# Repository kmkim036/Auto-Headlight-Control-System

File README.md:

# Program Language  
C    
# When  
Senior, 2nd semester in Automobile Electric System Design Class  
# Description  
## Automatic Headlight Control System
Measure data with Light sensor and Acceleration sensor  

Control LED and Servo Motor  

Use CAN communication to command

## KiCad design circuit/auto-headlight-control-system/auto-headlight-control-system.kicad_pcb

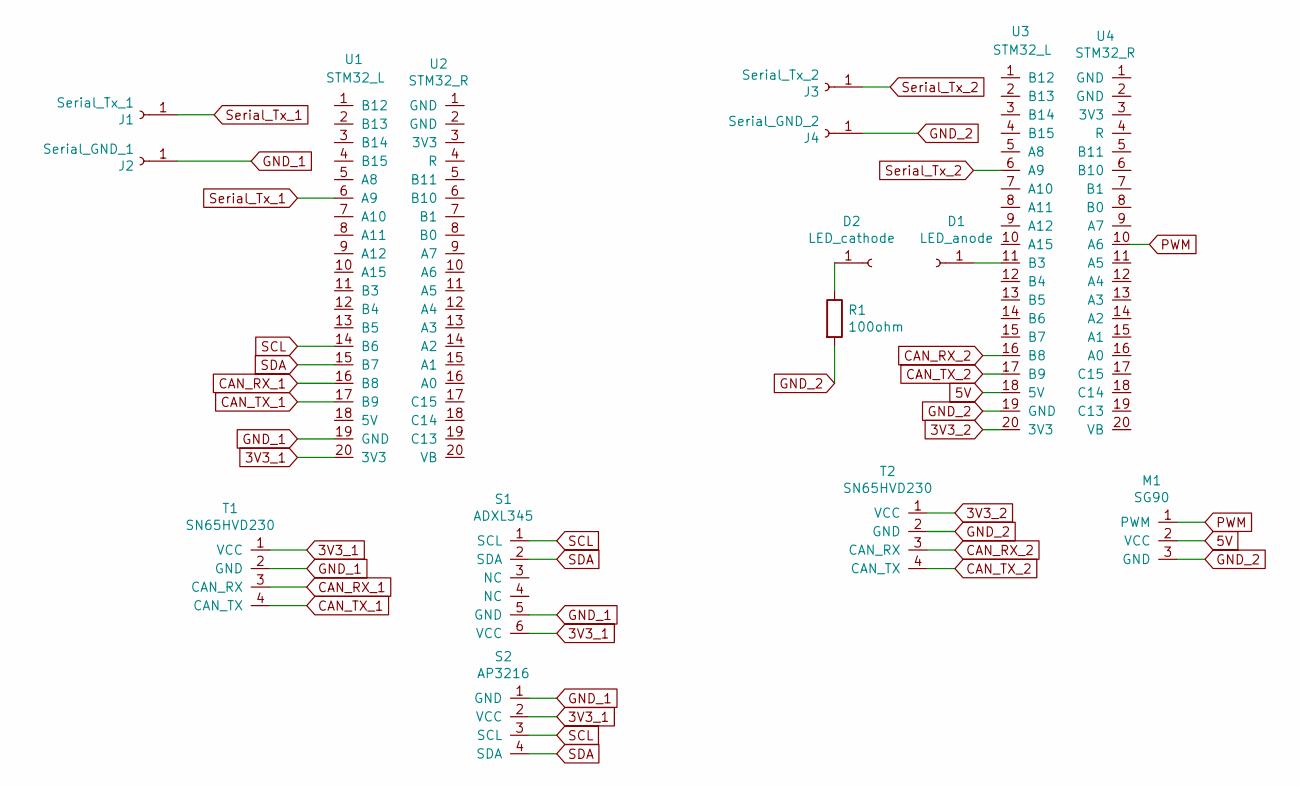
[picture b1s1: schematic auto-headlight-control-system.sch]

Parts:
D1: LED_anode; PinHeader_1x01_P2.54mm_Vertical
D2: LED_cathode; PinHeader_1x01_P2.54mm_Vertical
J1: Serial_Tx_1; PinSocket_1x01_P2.54mm_Vertical
J2: Serial_GND_1; PinSocket_1x01_P2.54mm_Vertical
J3: Serial_Tx_2; PinSocket_1x01_P2.54mm_Vertical
J4: Serial_GND_2; PinSocket_1x01_P2.54mm_Vertical
M1: SG90; PinHeader_1x03_P2.54mm_Vertical
R1: 100ohm; R_Axial_DIN0207_L6.3mm_D2.5mm_P2.54mm_Vertical
S1: ADXL345; PinHeader_1x06_P2.54mm_Vertical
S2: AP3216; PinHeader_1x04_P2.54mm_Vertical
T1, T2: SN65HVD230; PinHeader_1x04_P2.54mm_Vertical
U1, U3: STM32_L; PinHeader_1x20_P2.54mm_Vertical
U2, U4: STM32_R; PinHeader_1x20_P2.54mm_Vertical

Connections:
3V3_1: S1.6 (VCC), S2.2 (VCC), T1.1 (VCC), U1.20 (3V3)
3V3_2: T2.1 (VCC), U3.20 (3V3)
5V: M1.2 (VCC), U3.18 (5V)
CAN_RX_1: T1.3 (CAN_RX), U1.16 (B8)
CAN_RX_2: T2.3 (CAN_RX), U3.16 (B8)
CAN_TX_1: T1.4 (CAN_TX), U1.17 (B9)
CAN_TX_2: T2.4 (CAN_TX), U3.17 (B9)
GND_1: J2.1, S1.5 (GND), S2.1 (GND), T1.2 (GND), U1.19 (GND)
GND_2: J4.1, M1.3 (GND), R1.2, T2.2 (GND), U3.19 (GND)
unnamed: D1.1, U3.11 (B3)
unnamed: D2.1, R1.1
PWM: M1.1 (PWM), U4.10 (A6)
SCL: S1.1 (SCL), S2.3 (SCL), U1.14 (B6)
SDA: S1.2 (SDA), S2.4 (SDA), U1.15 (B7)
Serial_Tx_1: J1.1, U1.6 (A9)
Serial_Tx_2: J3.1, U3.6 (A9)

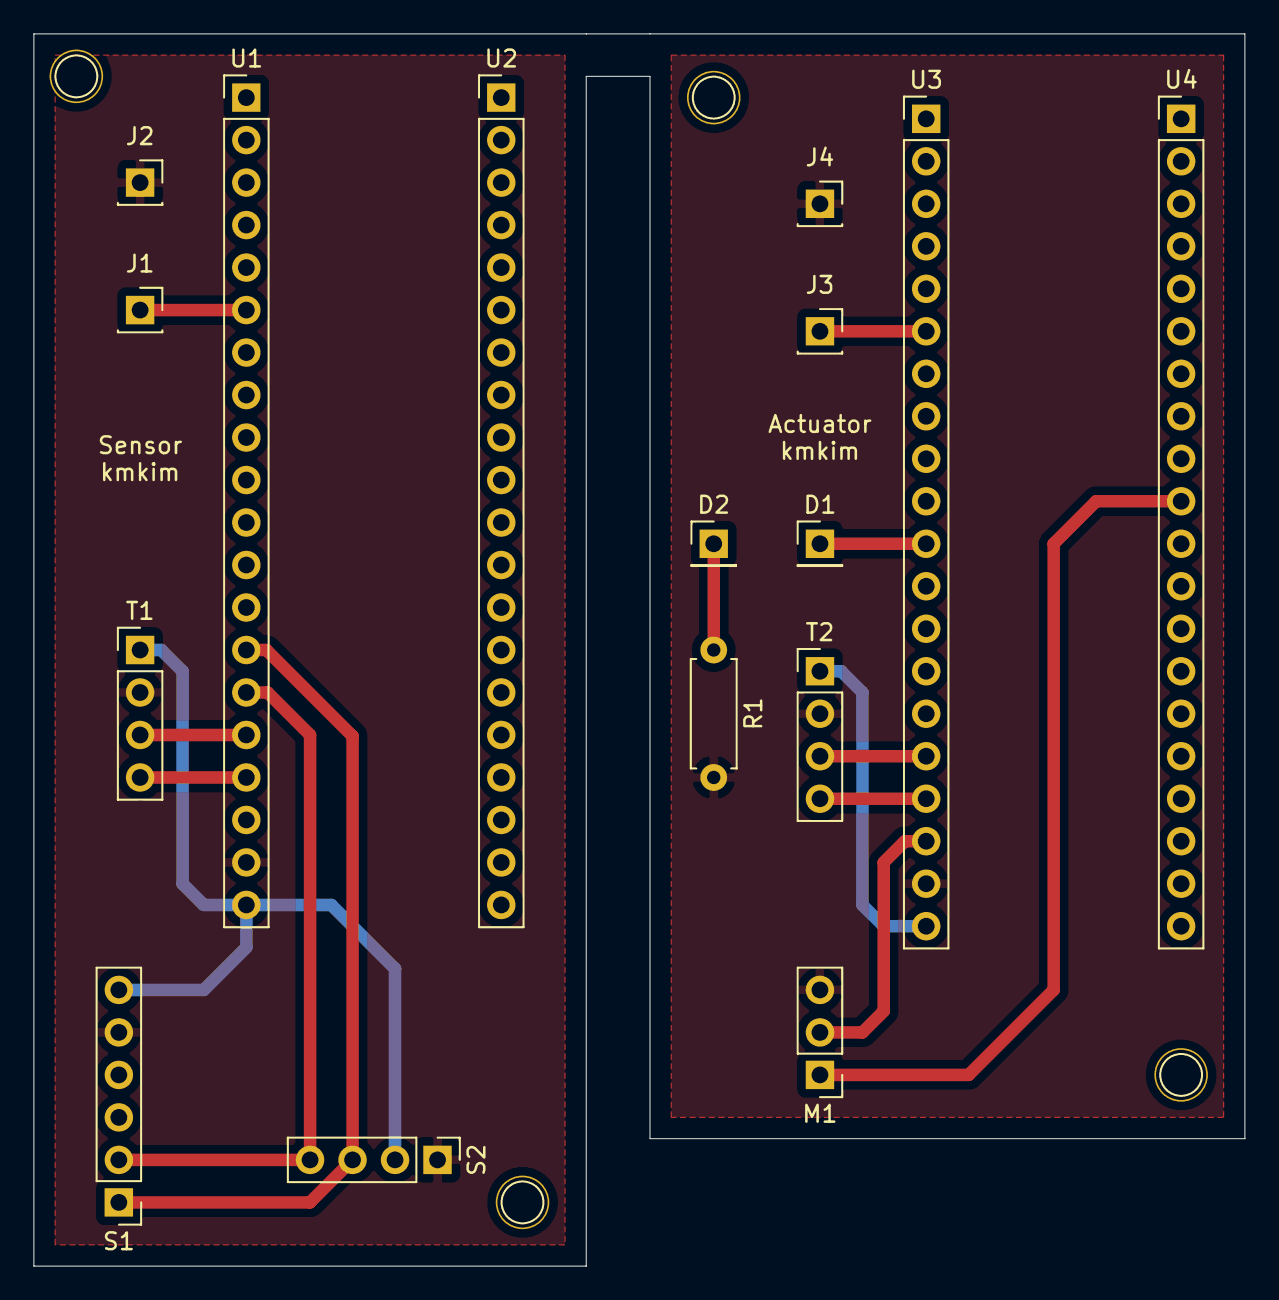
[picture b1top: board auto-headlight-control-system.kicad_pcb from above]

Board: 2 copper layers, 72.4 x 73.7 mm, 20 parts (0 on the bottom side), 16 nets.

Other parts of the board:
 : Pin_D1.0mm_L10.0mm
 #2,  #3,  #4: Pin_D1.0mm_L10.0mm

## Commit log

2021-11-12 Update: 211112 version
2021-11-14 Update: done before CAN
2021-11-15 Add: CAN network
2021-11-16 Fix: Description and When
2021-11-18 complete with CAN
2021-11-19 Add: KICAD project
2021-11-19 Formatting
2021-11-23 Compact: PCB
2021-11-25 Fix: PCB size
2021-11-29 Add: gerber and Fix
2021-11-29 Add: gerber
2021-11-30 Update: merge PCB
